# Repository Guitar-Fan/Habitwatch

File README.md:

# Habitwatch

This is the Habitwatch, a custom designed smartwatch for keep track of habits. It uses an Xiao ESP-32-C6 4.0 development board, compact enough to fit in a small sized enclosure, while having many features. The main function is a highly customizable reminder/alarm system, that works along side a integrated vibration motor to remind you to keep all habits you want. The firmware also allows users to customize the motor to produce a custom monophonic ringtone. Extra features include connectivity with devices via wifi, bluetooth, etc... All electronics are smarly housed in a custom-designed 3D-printed compact enclosure (with a reasonable size for a watch).

I made this project because I know first-hand the difficulty of upholding good habits, and wanted to make a project to help out with a common life problem. I also wanted this watch to be truely useful to everyday life.

## Images

### Schematic

*Complete wiring diagram showing all connections*

### PCB Design

*Custom PCB design for the Habitwatch circuit*

### 3D Enclosure - Front

*Custom-designed 3D-printed enclosure front view*

### 3D Enclosure - Back

*Custom-designed 3D-printed enclosure back view*

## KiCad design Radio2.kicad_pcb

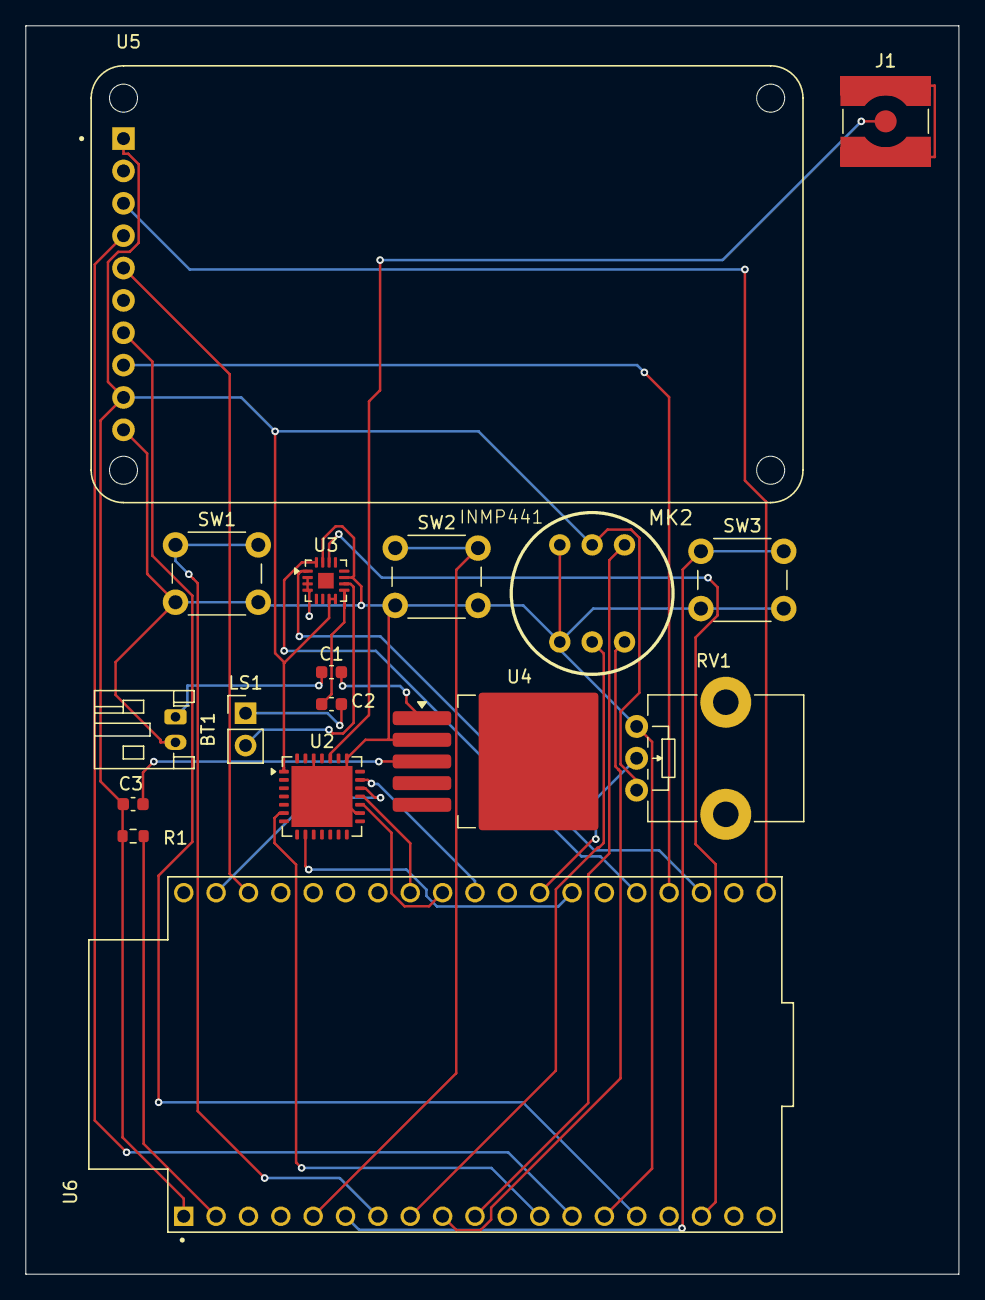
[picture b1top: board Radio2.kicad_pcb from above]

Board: 2 copper layers, 73.2 x 98.0 mm, 17 parts (0 on the bottom side), 31 nets.

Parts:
BT1: LiPo 3.7V 2000mAh (Adafruit #2011); JST_PH_S2B-PH-K_1x02_P2.00mm_Horizontal
C1: 10 µF; C_0603_1608Metric
C2, C3: 100 nF; C_0603_1608Metric
J1: Conn_Coaxial; SMA_Amphenol_132134-10_Vertical
LS1: 8Ω 0.5W speaker; PinHeader_1x02_P2.54mm_Vertical
MK2: INMP441
R1: 10 kΩ; R_0603_1608Metric
RV1: R_Potentiometer; Potentiometer_Bourns_PTV09A-1_Single_Vertical
SW1, SW2, SW3: SW_Push; SW_PUSH_6mm
U2: SX1272; QFN-28-1EP_6x6mm_P0.65mm_EP4.8x4.8mm
U3: MAX98357A; TQFN-16-1EP_3x3mm_P0.5mm_EP1.23x1.23mm
U4: MCP1826S; TO-263-5_TabPin6
U5: Industrial Monitor, Color LCD TFT, 1.8 in, 128 x 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; MODULE_358
U6: ESP32-DEVKITC V4; MODULE_ESP32-DEVKITC

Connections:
+3V3: C3.1, MK2.5 (3V3), R1.1, RV1.1, U2.1 (VBAT1), U3.7 (VDD), U3.8 (VDD), U5.1 (LITE), U5.9 (VCC), U6.1 (3V3)
GND: BT1.2 (-), MK2.1 (L/R), MK2.4 (GND), RV1.3, SW1.2, SW2.2, SW3.2, U2.16 (GND), U2.22 (GND), U2.26 (GND), U2.29 (GND), U3.2 (GAIN_SLOT), U3.3 (GND), U3.4 (~SD_MODE), U3.11 (GND), U3.15 (GND), U4.2 (GND), U5.10 (GND), U6.14 (GND1)
unnamed: BT1.1 (+), C1.1
unnamed: C2.2, LS1.1
unnamed: J1.1 (In), U2.24 (RFO)
unnamed: MK2.3 (SCK), U6.9 (IO25)
unnamed: MK2.6 (SD), U6.10 (IO26)
unnamed: MK2.2 (WS), U6.8 (IO33)
unnamed: U2.9 (DIO0), U6.26 (IO4)
unnamed: U2.18 (MISO), U6.31 (IO19)
unnamed: U2.19 (MOSI), U6.37 (IO23)
unnamed: U2.20 (NSS), U6.29 (IO5)
unnamed: U2.17 (SCK), U6.30 (IO18)
unnamed: U2.6 (~RESET), U6.12 (IO14)
unnamed: U3.16 (BCLK), U6.24 (IO2)
unnamed: U3.1 (DIN), U6.22 (SD1)
unnamed: U3.14 (LRCLK), U6.17 (SD3)
unnamed: LS1.2, U3.10 (OUTN)
unnamed: C2.1, U3.9 (OUTP)
unnamed: C1.2, U4.1 (VI)
unnamed: C3.2, U4.3 (VO)
unnamed: U5.7 (D/C), U6.15 (IO13)
unnamed: U5.4 (MOSI), U6.13 (IO12)
unnamed: U5.8 (RESET), U6.23 (IO15)
unnamed: U5.3 (SCK), U6.20 (CLK)
unnamed: U5.5 (TFT_CS), U6.36 (IO22)
unnamed: R1.2, U6.2 (EN)
unnamed: RV1.2, U6.27 (IO16)
unnamed: SW1.1, U6.7 (IO32)
unnamed: SW2.1, U6.5 (IO34)
unnamed: SW3.1, U6.6 (IO35)

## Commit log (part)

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2026-05-30 Implement HabitWatch OS v2.1 with various fixes
    This commit introduces the HabitWatch OS v2.1 for the Seeed Studio XIAO ESP32-C6 smartwatch. Key fixes include improved button event handling, non-blocking timers, and enhanced battery calculations.
2026-06-06 repo finished
2026-06-06 Add files via upload
    because stasis YSWS wouldn't accept easyeda format
